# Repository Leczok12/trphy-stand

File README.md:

# trphy-stand

## Usage

### Controller

Connect board to 5v (min 1A) power suply

<table>
    <tr>
        <td rowspan = "3"> </td>
        <td> POWER </td>
    </td>
    <tr>
        <td>NEXT EFFECT </td>
    </td>
    <tr>
        <td>PREVIOUS EFFECT</td>
    </td>
</table>

### Board

<table>
    <tr>
        <td>LED CONNECTOR</td>
        <td rowspan = "4"> </td>
        <td>SPEED ADJUSTMENT</td>
    </td>
    <tr>
        <td>SETTINGS ENABLE BUTTON</td>
        <td>BLUE COLOR ADJUSTMENT</td>
    </td>
    <tr>
        <td></td>
        <td>GREEN COLOR ADJUSTMENT</td>
    </td>
    <tr>
        <td>CONTROLLER CONNECTOR</td>
        <td>RED COLOR ADJUSTMENT</td>
    </td>
</table>

## Appearance

<table>
    <tr>
        <td> </td>
        <td> </td>    
    </td>
    <tr>
        <td> </td>
        <td> </td>    
    </td>
</table>

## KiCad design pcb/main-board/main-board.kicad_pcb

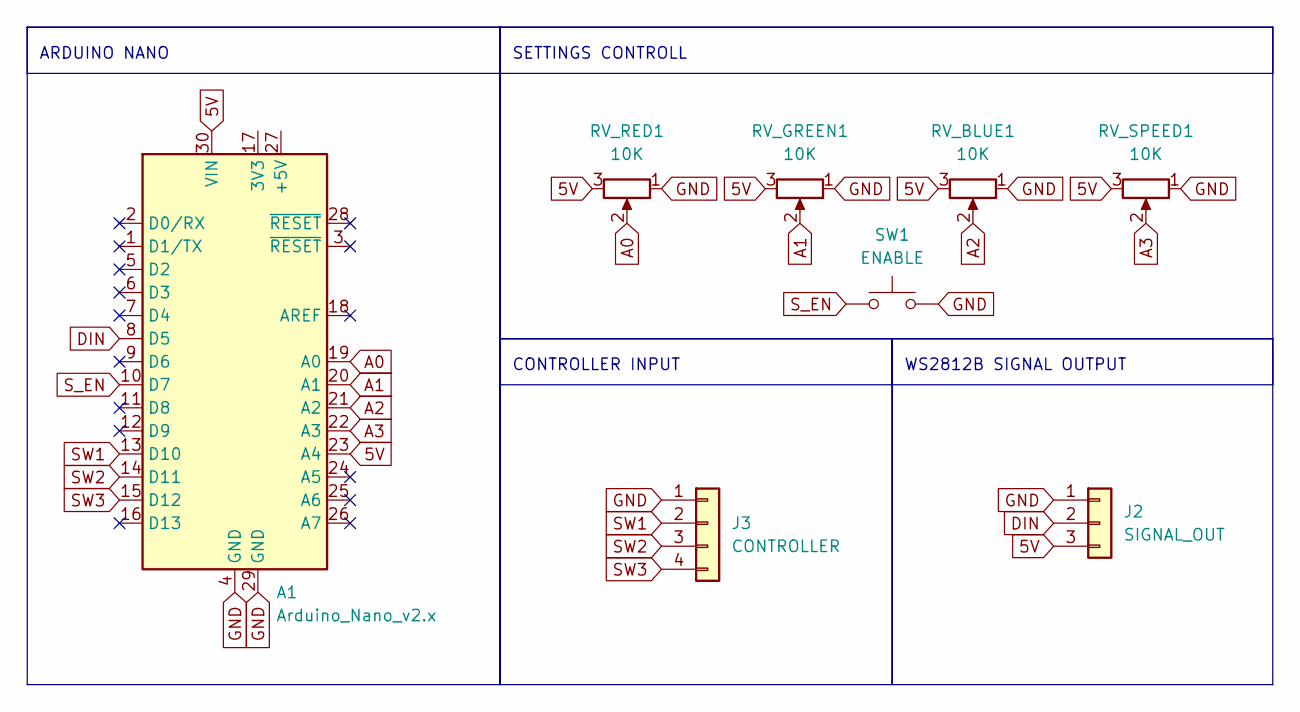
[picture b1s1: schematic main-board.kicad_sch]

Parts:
A1: Arduino_Nano_v2.x; Arduino_Nano
J2: SIGNAL_OUT; JST_XH_S3B-XH-A-1_1x03_P2.50mm_Horizontal
J3: CONTROLLER; JST_XH_S4B-XH-A-1_1x04_P2.50mm_Horizontal
RV_BLUE1: 10K; Potentiometer_ACP_CA9-H5_Horizontal
RV_GREEN1: 10K; Potentiometer_ACP_CA9-H5_Horizontal
RV_RED1: 10K; Potentiometer_ACP_CA9-H5_Horizontal
RV_SPEED1: 10K; Potentiometer_ACP_CA9-H5_Horizontal
SW1: ENABLE; SW_PUSH-12mm

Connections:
5V: A1.23 (A4), A1.30 (VIN), J2.3, RV_BLUE1.3, RV_GREEN1.3, RV_RED1.3, RV_SPEED1.3
A0: A1.19 (A0), RV_RED1.2
A1: A1.20 (A1), RV_GREEN1.2
A2: A1.21 (A2), RV_BLUE1.2
A3: A1.22 (A3), RV_SPEED1.2
DIN: A1.8 (D5), J2.2
GND: A1.4 (GND), A1.29 (GND), J2.1, J3.1, RV_BLUE1.1, RV_GREEN1.1, RV_RED1.1, RV_SPEED1.1, SW1.2
SW1: A1.13 (D10), J3.2
SW2: A1.14 (D11), J3.3
SW3: A1.15 (D12), J3.4
S_EN: A1.10 (D7), SW1.1

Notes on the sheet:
WS2812B SIGNAL OUTPUT
ARDUINO NANO
CONTROLLER INPUT
SETTINGS CONTROLL

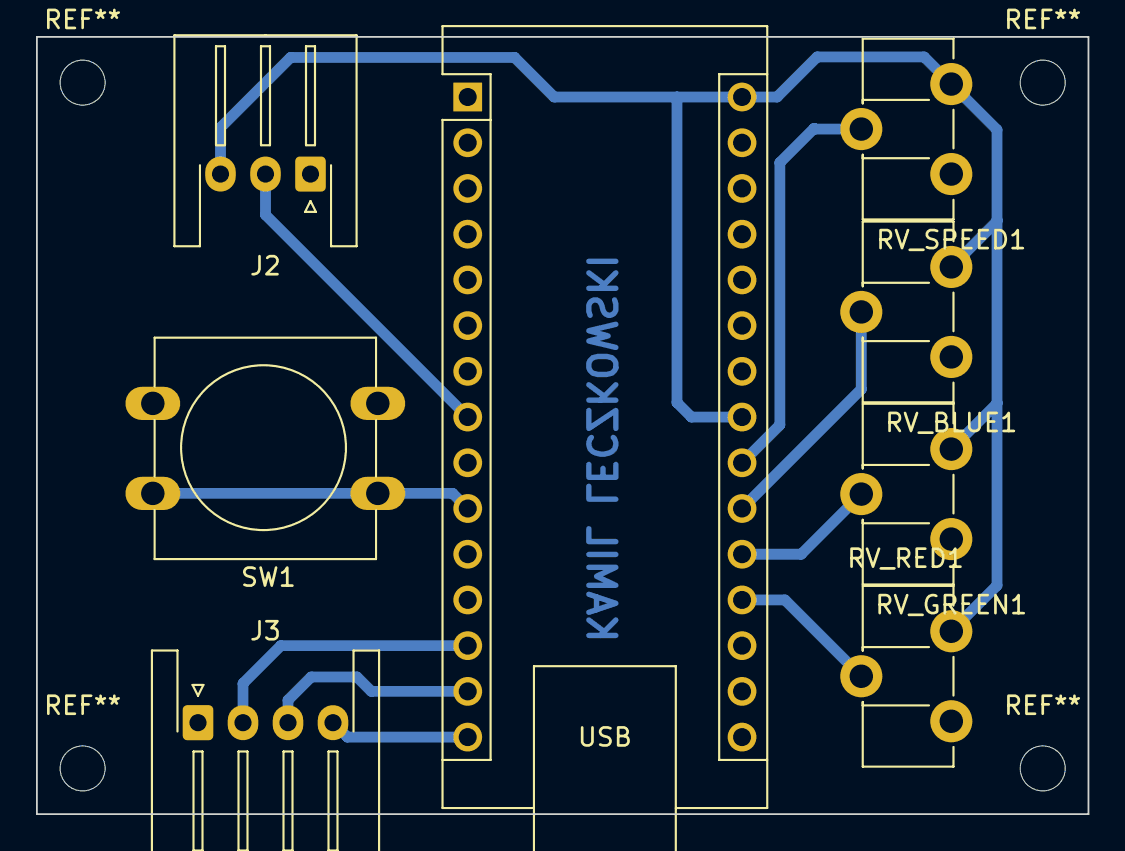
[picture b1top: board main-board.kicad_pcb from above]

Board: 2 copper layers, 58.4 x 43.2 mm, 8 parts (0 on the bottom side), 11 nets.

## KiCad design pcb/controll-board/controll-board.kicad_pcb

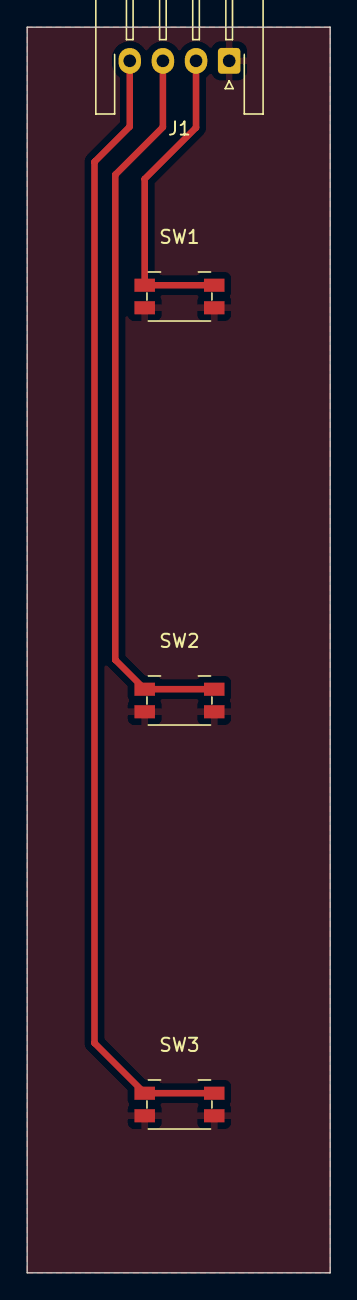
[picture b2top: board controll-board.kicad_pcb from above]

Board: 2 copper layers, 22.9 x 94.0 mm, 4 parts (0 on the bottom side), 4 nets.

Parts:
J1: CONTROLLER; JST_XH_S4B-XH-A-1_1x04_P2.50mm_Horizontal
SW1, SW2, SW3: SW_Push; Panasonic_EVQPUJ_EVQPUA

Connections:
GND: J1.1, SW1.2, SW2.2, SW3.2
SW1: J1.2, SW1.1
SW2: J1.3, SW2.1
SW3: J1.4, SW3.1

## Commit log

2024-03-07 created pcb boards
2024-03-17 project finished
2024-03-19 readme
